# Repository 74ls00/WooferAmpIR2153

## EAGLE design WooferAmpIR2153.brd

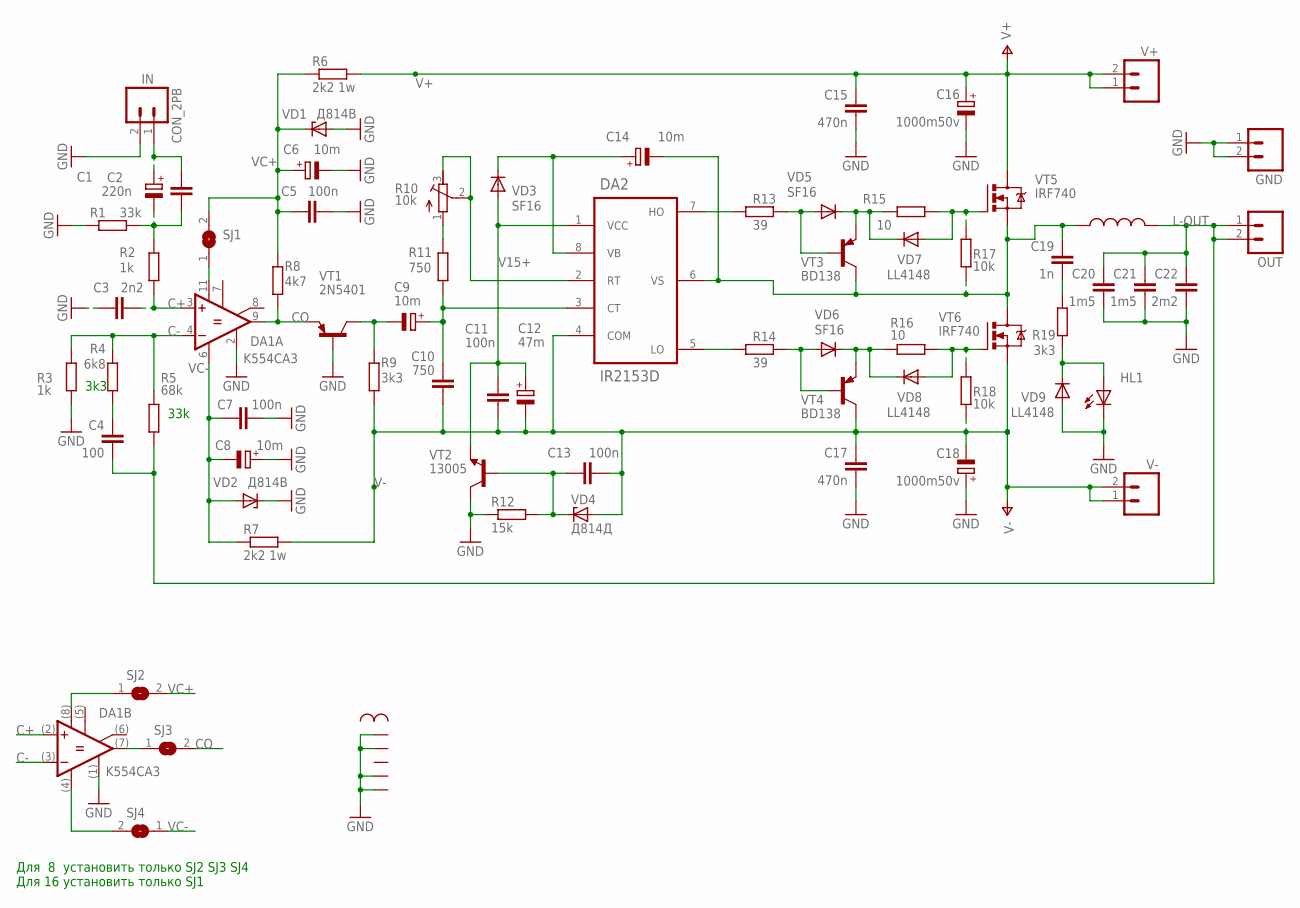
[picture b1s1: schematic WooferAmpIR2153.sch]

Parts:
C1: CPOL-EUE2.5-6; E2,5-6
C2: 220n; C050-025X075
C3: 2n2; C050-025X075
C4: 100; C_11X3.5
C5: 100n; C075-032X103
C6, C8, C9, C14: 10m; E2,5-6
C7, C11, C13: 100n; C050-025X075
C10: 750; C075-032X103
C12: 47m; E2,5-6
C15, C17: 470n; C150-072X183
C16, C18: 1000m50v; E7,5-18
C19: 1n; C050-025X075
C20, C21: 1m5; C_22X13
C22: 2m2; C_23X16
DA1: K554CA3; DIL_A(14)
DA2: IR2153D; DIL8
GND: CON_2PA; CON_PWR_2PIN4MM
HL1: LED3MM
IN: CON_2PB; CON_PWRI_2PIN4MM
OUT: CON_2PA; CON_PWR_2PIN4MM
R1: 33k; 0207/10
R2: 1k; 0207/10
R3: 1k; M0805
R4: 6k8; M0805
R5: 68k; M1206
R6, R7: 2k2 1w; P0613/15
R8: 4k7; M0805
R9: 3k3; 0207/10
R10: 10k; RTRIM3296W
R11: 750; M0805
R12: 15k; 0207/10
R13, R14: 39; M1206
R15, R16: 10; M1206
R17, R18: 10k; M1206
R19: 3k3; M1206
SJ1, SJ2, SJ3, SJ4: SJ
U$1: L-D30
U$4, U$11: PIN; PIN-L
V+: CON_2PA; CON_PWR_2PIN4MM
V-: CON_2PA; CON_PWR_2PIN4MM
VD1, VD2: Д814В; ZDMETAL
VD3, VD5, VD6: SF16; DO204-10
VD4: Д814Д; ZDMETAL
VD7, VD8, VD9: LL4148; SOD80C
VT1: 2N5401; TO92
VT2: 13005; TO220FV
VT3, VT4: BD138; TO126V
VT5, VT6: IRF740; TO220

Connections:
C+: C3.2, DA1.3 (+IN), DA1.(2) (+IN), R2.2
C-: DA1.4 (-IN), DA1.(3) (-IN), R3.2, R4.2, R5.2
CO: DA1.9 (OUT), R8.1, SJ3.2, VT1.1 (E)
GATE_A: R15.2, R17.2, VD7.A, VT5.1 (G)
GND: C3.1, C5.2, C6.-, C7.2, C8.+, C15.2, C16.-, C17.2, C18.+, C20.2, C21.2, C22.2, DA1.2 (GND), DA1.(1) (GND), GND.1, GND.2, HL1.K (C), IN.2, R1.2, R3.1, R12.1, U$1.1A, U$1.1B, U$1.2B, U$1.D, VD1.A, VD2.C, VD9.A, VT1.2 (B), VT2.2 (C)
L-OUT: C4.2, C20.1, C21.1, C22.1, OUT.1, OUT.2, R5.1, U$11.P$1
unnamed: DA2.2 (RT), R10.2 (S), R10.3 (A)
unnamed: C13.1, R12.2, VD4.C, VT2.1 (B)
unnamed: C9.+, C10.1, DA2.3 (CT), R11.2
unnamed: R10.1 (E), R11.1
unnamed: C4.1, R4.1
unnamed: DA1.11 (V+), SJ1.1
unnamed: C19.2, R19.2
unnamed: HL1.A, R19.1, VD9.C
unnamed: DA2.7 (HO), R13.1
unnamed: DA2.5 (LO), R14.1
unnamed: R16.1, VD6.C, VD8.C, VT4.1 (E)
unnamed: R14.2, VD6.A, VT4.3 (B)
unnamed: R15.1, VD5.C, VD7.C, VT3.1 (E)
unnamed: R13.2, VD5.A, VT3.3 (B)
unnamed: R16.2, R18.2, VD8.A, VT6.1 (G)
unnamed: C1.+, C2.1, IN.1
unnamed: C1.-, C2.2, R1.1, R2.1
unnamed: DA1.(7) (OUT), SJ3.1
unnamed: DA1.(4) (V-), SJ4.2
unnamed: DA1.(8) (V+), SJ2.1
unnamed: C9.-, R9.1, VT1.3 (C)
NL: C14.-, C19.1, DA2.6 (VS), R17.1, U$4.P$1, VT3.2 (C), VT5.3 (S), VT6.2 (D)
V15+: C11.1, C12.+, DA2.1 (VCC), VD3.A, VT2.3 (E)
V+: C15.1, C16.+, R6.2, V+.1, V+.2, VT5.2 (D)
V-: C10.2, C11.2, C12.-, C13.2, C17.1, C18.-, DA2.4 (COM), R7.2, R9.2, R18.1, V-.1, V-.2, VD4.A, VT4.2 (C), VT6.3 (S)
VB: C14.+, DA2.8 (VB), VD3.C
VC+: C5.1, C6.+, R6.1, R8.2, SJ1.2, SJ2.2, VD1.C
VC-: C7.1, C8.-, DA1.6 (V-), R7.1, SJ4.1, VD2.A

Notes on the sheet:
33k
3k3
Для 8 установить только SJ2 SJ3 SJ4 Для 16 установить только SJ1

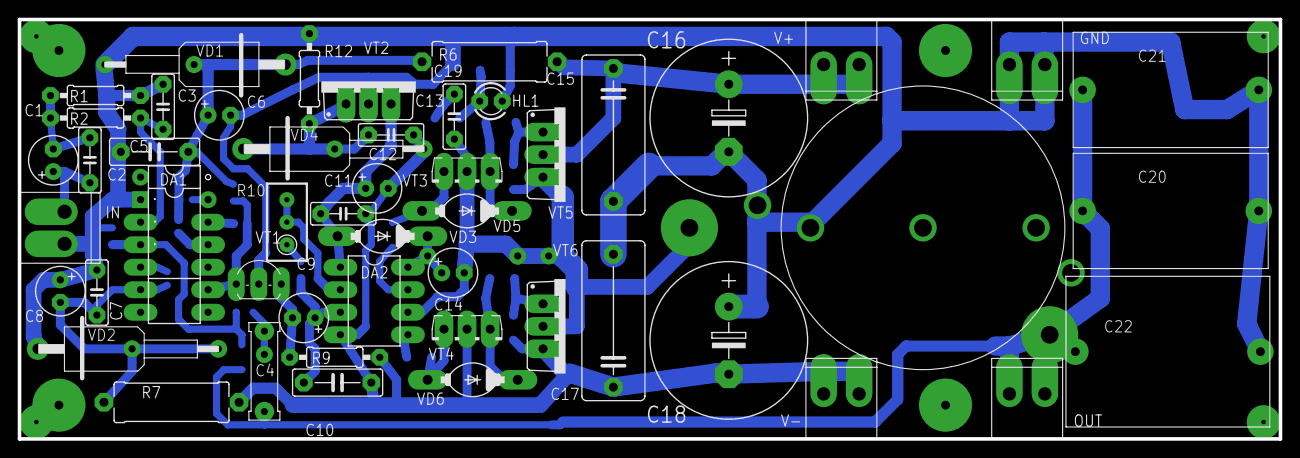
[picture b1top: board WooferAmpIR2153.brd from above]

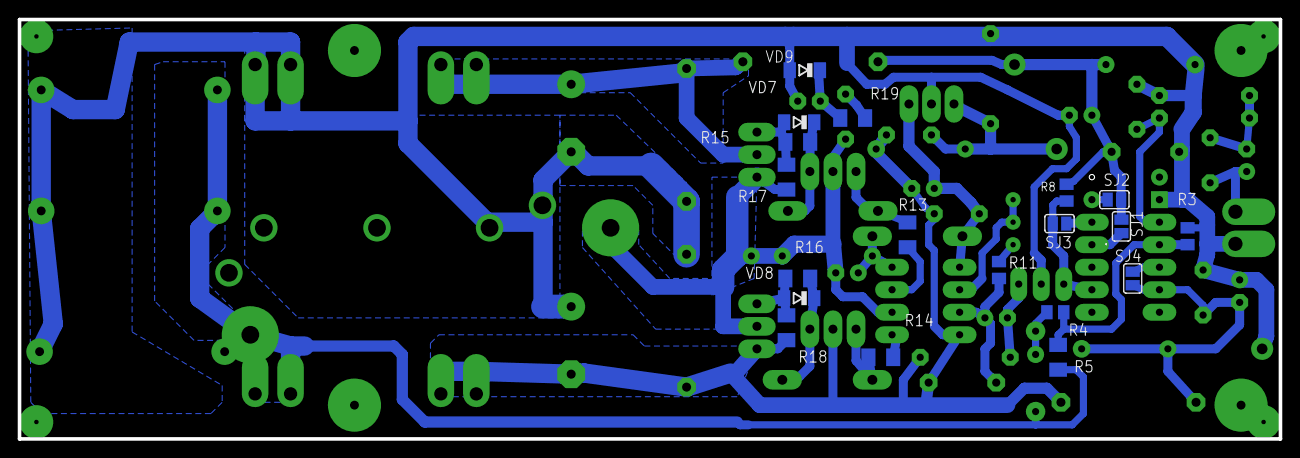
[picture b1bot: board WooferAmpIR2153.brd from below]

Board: 2 copper layers, 142.2 x 47.3 mm, 71 parts (19 on the bottom side), 34 nets.

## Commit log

2019-04-05 rel 1
2019-04-05 rel 2
2019-04-06 fix2
2019-04-08 hm10
2019-04-08 rel3
2019-04-11 rel4
